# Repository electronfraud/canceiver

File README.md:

# CANceiver

**WORK IN PROGRESS**

A CAN-to-USB adapter. Built so I could get some experience with CAN, USB, and STM32 microcontrollers.

## Firmware

Yet to come.

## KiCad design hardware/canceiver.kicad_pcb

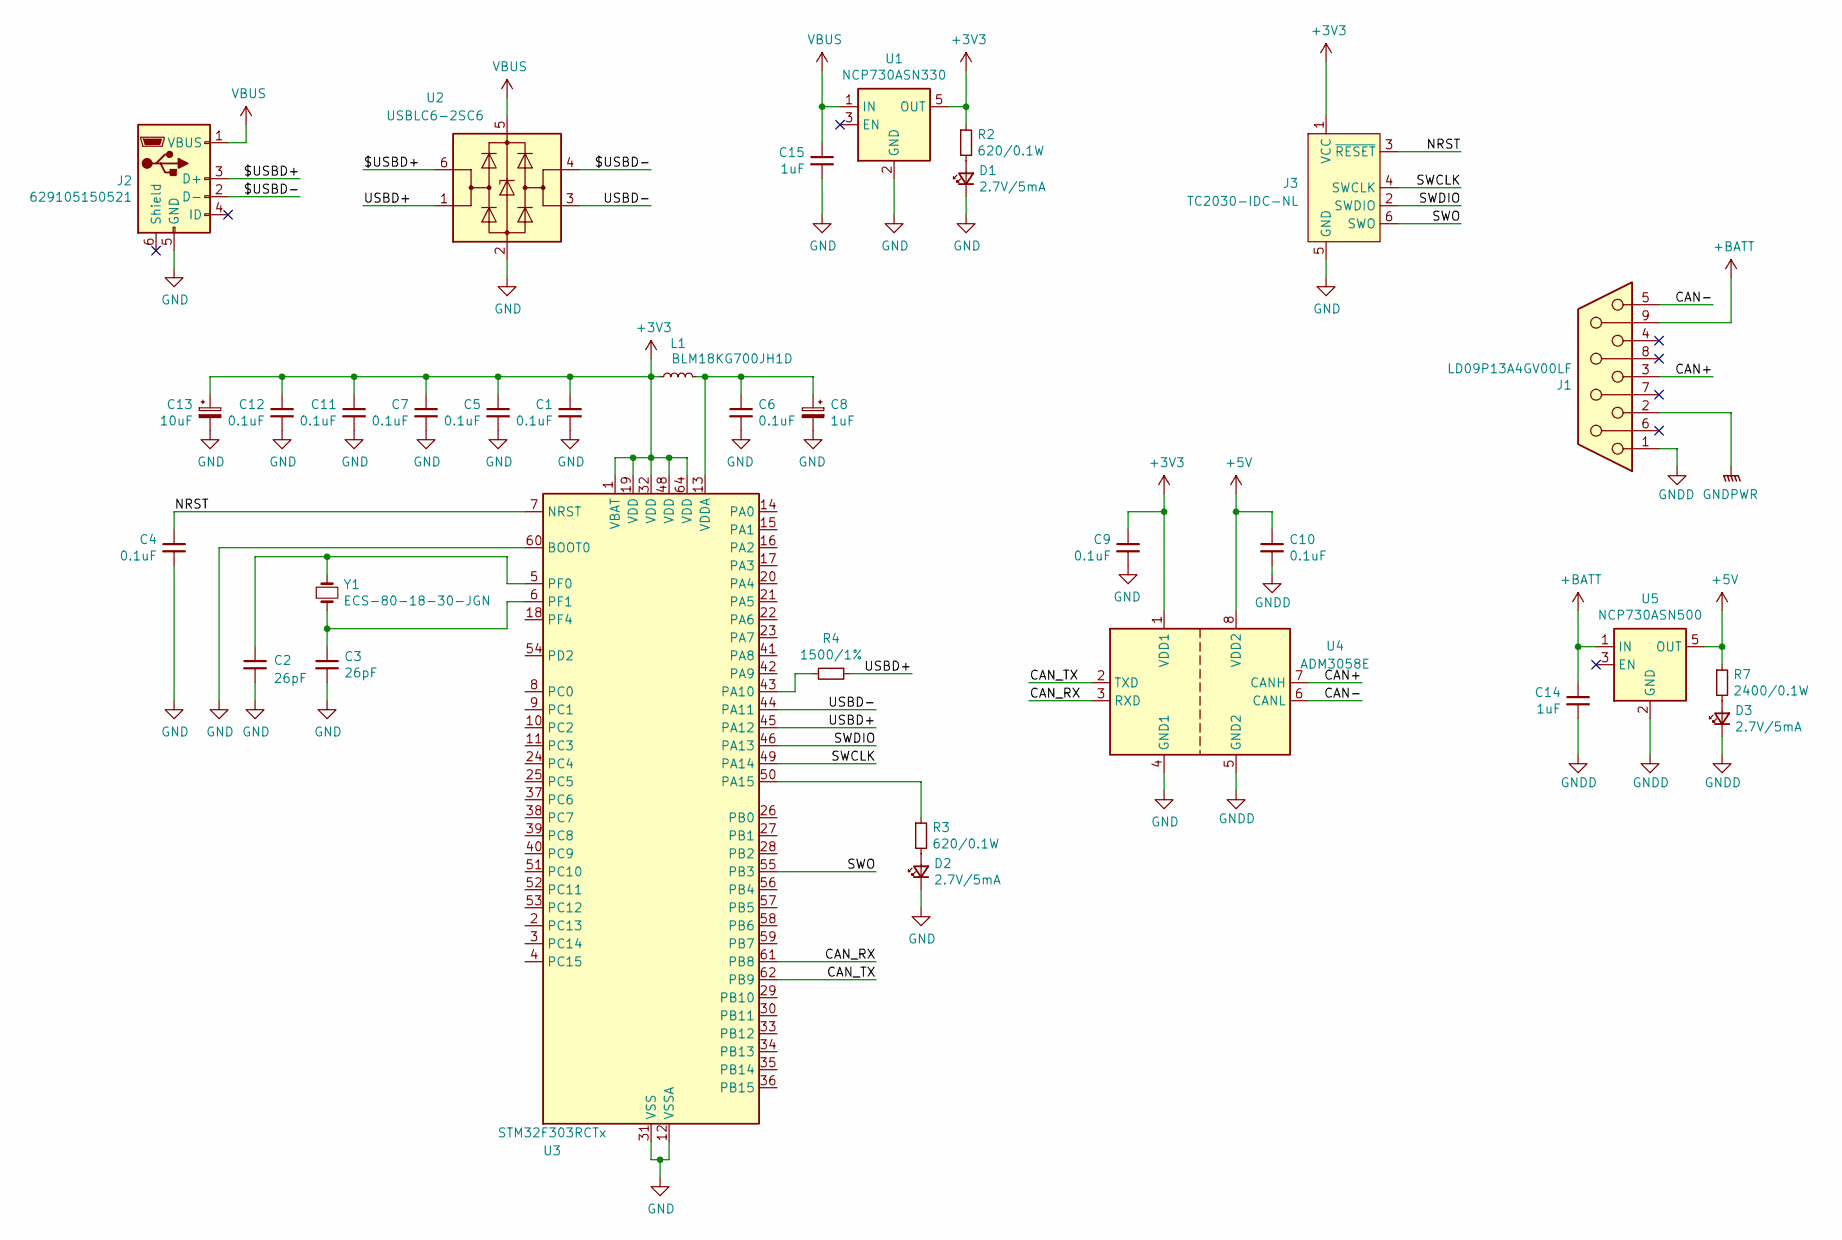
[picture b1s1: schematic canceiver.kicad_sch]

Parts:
C1, C4, C5, C6, C7, C9, C10, C11, C12: 0.1uF; C_0603_1608Metric
C2, C3: 26pF; C_0603_1608Metric
C8: 1uF; CP_EIA-3216-18_Kemet-A
C13: 10uF; CP_EIA-3216-18_Kemet-A
C14, C15: 1uF; C_0603_1608Metric
D1, D2, D3: 2.7V/5mA; LED_0603_1608Metric
J1: LD09P13A4GV00LF; DSUB-9_Female_Horizontal_P2.77x2.84mm_EdgePinOffset9.90mm_H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
J2: 629105150521; USB_Micro-B_Wuerth_629105150521
J3: TC2030-IDC-NL; Tag-Connect_TC2030-IDC-NL_2x03_P1.27mm_Vertical
L1: BLM18KG700JH1D; L_0603_1608Metric
R2, R3: 620/0.1W; R_0603_1608Metric
R4: 1500/1%; R_0603_1608Metric
R7: 2400/0.1W; R_0603_1608Metric
U1: NCP730ASN330; SOT-23-5
U2: USBLC6-2SC6; SOT-23-6
U3: STM32F303RCTx; LQFP-64_10x10mm_P0.5mm
U4: ADM3058E; SOIC-8_7.5x5.85mm_P1.27mm
U5: NCP730ASN500; SOT-23-5
Y1: ECS-80-18-30-JGN; Crystal_SMD_5032-2Pin_5.0x3.2mm

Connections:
+3V3: C1.1, C5.1, C7.1, C9.1, C11.1, C12.1, C13.1, J3.1 (VCC), L1.1, R2.1, U1.5 (OUT), U3.1 (VBAT), U3.19 (VDD), U3.32 (VDD), U3.48 (VDD), U3.64 (VDD), U4.1 (VDD1)
+5V: C10.1, R7.1, U4.8 (VDD2), U5.5 (OUT)
+BATT: C14.1, J1.9, U5.1 (IN)
/$USBD+: J2.3 (D+), U2.6 (I/O1)
/$USBD-: J2.2 (D-), U2.4 (I/O2)
/CAN+: J1.3, U4.7 (CANH)
/CAN-: J1.5, U4.6 (CANL)
/CAN_RX: U3.61 (PB8), U4.3 (RXD)
/CAN_TX: U3.62 (PB9), U4.2 (TXD)
/NRST: C4.1, J3.3 (~RESET), U3.7 (NRST)
/SWCLK: J3.4 (SWCLK), U3.49 (PA14)
/SWDIO: J3.2 (SWDIO), U3.46 (PA13)
/SWO: J3.6 (SWO), U3.55 (PB3)
/USBD+: R4.1, U2.1 (I/O1), U3.45 (PA12)
/USBD-: U2.3 (I/O2), U3.44 (PA11)
GND: C1.2, C2.2, C3.2, C4.2, C5.2, C6.2, C7.2, C8.2, C9.2, C11.2, C12.2, C13.2, C15.2, D1.1 (K), D2.1 (K), J2.5 (GND), J3.5 (GND), U1.2 (GND), U2.2 (GND), U3.12 (VSSA), U3.31 (VSS), U3.47 (VSS), U3.60 (BOOT0), U3.63 (VSS), U4.4 (GND1)
GNDPWR: J1.2
GNDS: C10.2, C14.2, D3.1 (K), J1.1, U4.5 (GND2), U5.2 (GND)
unnamed: D1.2 (A), R2.2
unnamed: D2.2 (A), R3.2
unnamed: D3.2 (A), R7.2
unnamed: R4.2, U3.43 (PA10)
unnamed: R3.1, U3.50 (PA15)
unnamed: C2.1, U3.5 (PF0), Y1.1
unnamed: C3.1, U3.6 (PF1), Y1.2
unnamed: C6.1, C8.1, L1.2, U3.13 (VDDA)
VBUS: C15.1, J2.1 (VBUS), U1.1 (IN), U2.5 (VBUS)

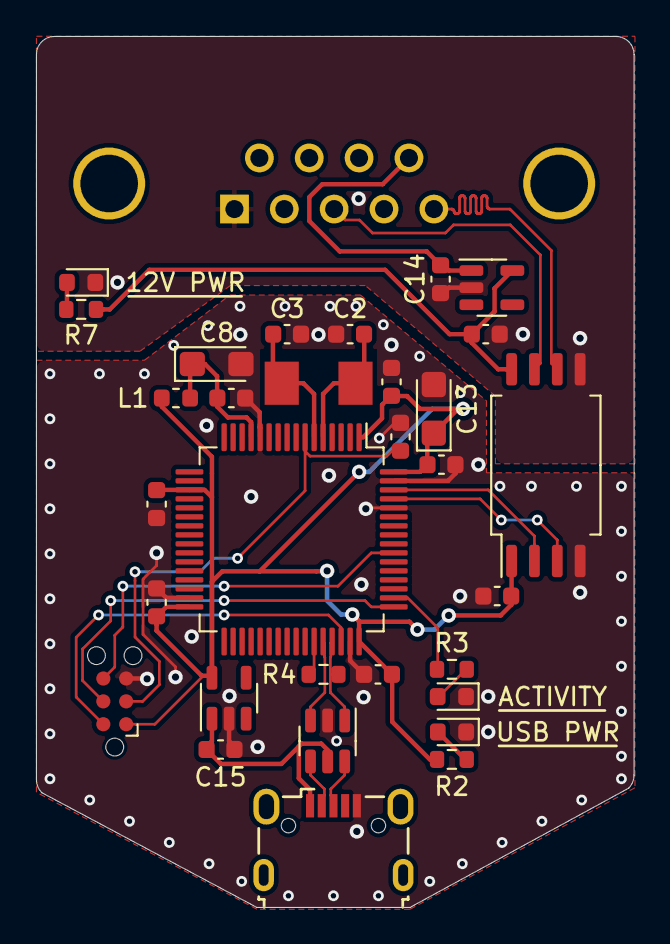
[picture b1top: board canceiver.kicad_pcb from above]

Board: 2 copper layers, 33.2 x 48.4 mm, 32 parts (0 on the bottom side), 26 nets.

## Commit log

2023-03-03 upgrade to kicad 7
2023-03-03 add plot workflow
2023-03-03 no-op change to force plot workflow to run
2023-03-03 plot schematics
